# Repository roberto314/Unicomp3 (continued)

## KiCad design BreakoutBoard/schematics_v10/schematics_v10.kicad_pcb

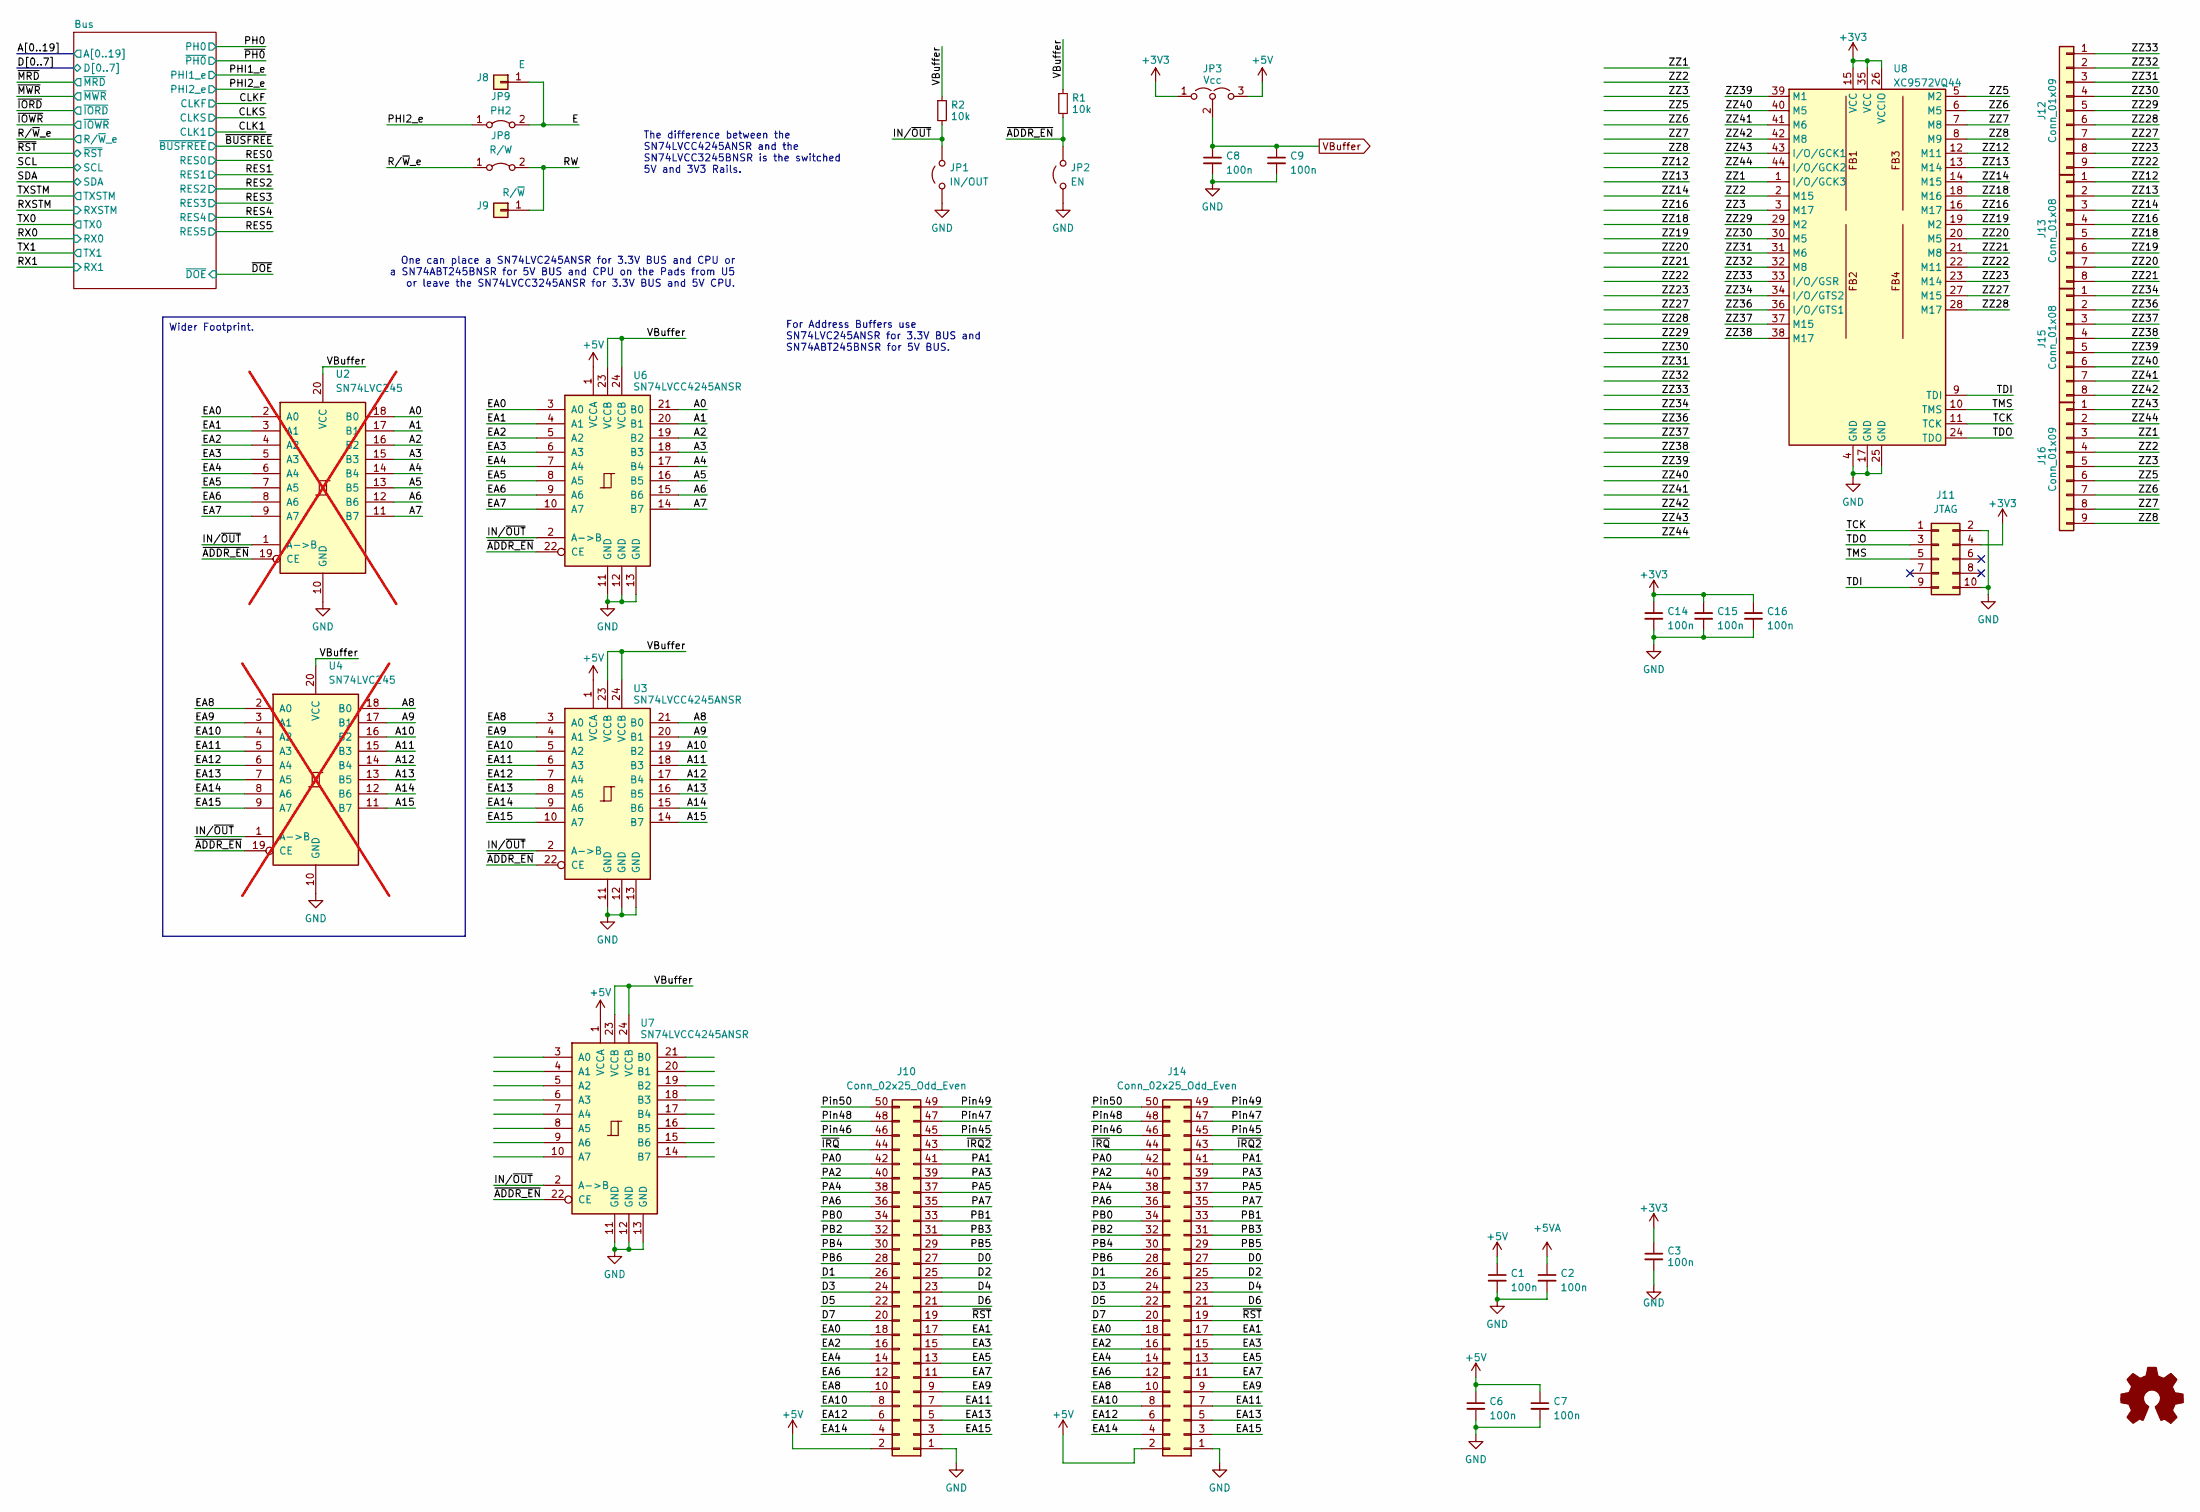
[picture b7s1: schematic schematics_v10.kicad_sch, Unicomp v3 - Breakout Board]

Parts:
C1, C2, C3, C6, C7, C8, C9, C14, C15, C16: 100n; C_1206_3216Metric
J8: E; PinHeader_1x01_P2.00mm_Vertical
J9: R/~{W}; PinHeader_1x01_P2.00mm_Vertical
J10: Conn_02x25_Odd_Even; PinHeader_2x25_P2.54mm_Vertical
J11: JTAG; PinHeader_2x05_P2.54mm_Horizontal
J12, J16: Conn_01x09; PinHeader_1x09_P2.54mm_Vertical
J13, J15: Conn_01x08; PinHeader_1x08_P2.54mm_Vertical
J14: Conn_02x25_Odd_Even; PinHeader_2x25_P2.54mm_Horizontal
JP1: IN/OUT; PinHeader_1x02_P2.54mm_Vertical
JP2: EN; PinHeader_1x02_P2.54mm_Vertical
JP3: Vcc; SolderJumper-3_P1.3mm_Open_RoundedPad1.0x1.5mm_NumberLabels
JP8: R/W; SolderJumper-2_P1.3mm_Bridged_RoundedPad1.0x1.5mm
JP9: PH2; SolderJumper-2_P1.3mm_Bridged_RoundedPad1.0x1.5mm
R1, R2: 10k; R_1206_3216Metric_Pad1.30x1.75mm_HandSolder
U2, U4: SN74LVC245; SO-20_12.8x7.5mm_P1.27mm; not fitted
U3, U6, U7: SN74LVCC4245ANSR; SO-24_5.3x15mm_P1.27mm
U8: XC9572VQ44; TQFP-44_10x10mm_P0.8mm

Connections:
+3V3: C3.1, C14.1, C15.1, C16.1, J11.4, JP3.1 (A), U8.15 (VCC), U8.26 (VCCIO), U8.35 (VCC); also elsewhere on the board
+5V: C1.1, C6.1, C7.1, J10.2, J14.2, JP3.3 (B), U3.1 (VCCA), U6.1 (VCCA), U7.1 (VCCA); also elsewhere on the board
+5VA: C2.1; also elsewhere on the board
/A0: U2.18 (B0), U6.21 (B0); also elsewhere on the board
/A1: U2.17 (B1), U6.20 (B1); also elsewhere on the board
/A2: U2.16 (B2), U6.19 (B2); also elsewhere on the board
/A3: U2.15 (B3), U6.18 (B3); also elsewhere on the board
/A4: U2.14 (B4), U6.17 (B4); also elsewhere on the board
/A5: U2.13 (B5), U6.16 (B5); also elsewhere on the board
/A6: U2.12 (B6), U6.15 (B6); also elsewhere on the board
/A7: U2.11 (B7), U6.14 (B7); also elsewhere on the board
/A8: U3.21 (B0), U4.18 (B0); also elsewhere on the board
/A9: U3.20 (B1), U4.17 (B1); also elsewhere on the board
/A10: U3.19 (B2), U4.16 (B2); also elsewhere on the board
/A11: U3.18 (B3), U4.15 (B3); also elsewhere on the board
/A12: U3.17 (B4), U4.14 (B4); also elsewhere on the board
/A13: U3.16 (B5), U4.13 (B5); also elsewhere on the board
/A14: U3.15 (B6), U4.12 (B6); also elsewhere on the board
/A15: U3.14 (B7), U4.11 (B7); also elsewhere on the board
/D0: J10.27, J14.27; also elsewhere on the board
/D1: J10.26, J14.26; also elsewhere on the board
/D2: J10.25, J14.25; also elsewhere on the board
/D3: J10.24, J14.24; also elsewhere on the board
/D4: J10.23, J14.23; also elsewhere on the board
/D5: J10.22, J14.22; also elsewhere on the board
/D6: J10.21, J14.21; also elsewhere on the board
/D7: J10.20, J14.20; also elsewhere on the board
/E: J8.1, JP9.2 (B)
/EA0: J10.18, J14.18, U2.2 (A0), U6.3 (A0)
/EA1: J10.17, J14.17, U2.3 (A1), U6.4 (A1)
/EA2: J10.16, J14.16, U2.4 (A2), U6.5 (A2)
/EA3: J10.15, J14.15, U2.5 (A3), U6.6 (A3)
/EA4: J10.14, J14.14, U2.6 (A4), U6.7 (A4)
/EA5: J10.13, J14.13, U2.7 (A5), U6.8 (A5)
/EA6: J10.12, J14.12, U2.8 (A6), U6.9 (A6)
/EA7: J10.11, J14.11, U2.9 (A7), U6.10 (A7)
/EA8: J10.10, J14.10, U3.3 (A0), U4.2 (A0)
/EA9: J10.9, J14.9, U3.4 (A1), U4.3 (A1)
/EA10: J10.8, J14.8, U3.5 (A2), U4.4 (A2)
/EA11: J10.7, J14.7, U3.6 (A3), U4.5 (A3)
/EA12: J10.6, J14.6, U3.7 (A4), U4.6 (A4)
/EA13: J10.5, J14.5, U3.8 (A5), U4.7 (A5)
/EA14: J10.4, J14.4, U3.9 (A6), U4.8 (A6)
/EA15: J10.3, J14.3, U3.10 (A7), U4.9 (A7)
/IN/~OUT: JP1.2 (B), R2.2, U2.1 (A->B), U3.2 (A->B), U4.1 (A->B), U6.2 (A->B), U7.2 (A->B)
/PA0: J10.42, J14.42
/PA1: J10.41, J14.41
/PA2: J10.40, J14.40
/PA3: J10.39, J14.39
/PA4: J10.38, J14.38
/PA5: J10.37, J14.37
/PA6: J10.36, J14.36
/PA7: J10.35, J14.35
/PB0: J10.34, J14.34
/PB1: J10.33, J14.33
/PB2: J10.32, J14.32
/PB3: J10.31, J14.31
/PB4: J10.30, J14.30
/PB5: J10.29, J14.29
/PB6: J10.28, J14.28
/PHI2_e: JP9.1 (A); also elsewhere on the board
/Pin45: J10.45, J14.45
/Pin46: J10.46, J14.46
/Pin47: J10.47, J14.47
/Pin48: J10.48, J14.48
/Pin49: J10.49, J14.49
/Pin50: J10.50, J14.50
/RW: J9.1, JP8.2 (B)
/R/~W_e: JP8.1 (A); also elsewhere on the board
/TCK: J11.1, U8.11 (TCK)
/TDI: J11.9, U8.9 (TDI)
/TDO: J11.3, U8.24 (TDO)
/TMS: J11.5, U8.10 (TMS)
/ZZ1: J16.3, U8.1 (I/O/GCK3)
/ZZ2: J16.4, U8.2 (M15)
/ZZ3: J16.5, U8.3 (M17)
/ZZ5: J16.6, U8.5 (M2)
/ZZ6: J16.7, U8.6 (M5)
/ZZ7: J16.8, U8.7 (M8)
/ZZ8: J16.9, U8.8 (M9)
/ZZ12: J13.1, U8.12 (M11)
/ZZ13: J13.2, U8.13 (M14)
/ZZ14: J13.3, U8.14 (M15)
/ZZ16: J13.4, U8.16 (M17)
/ZZ18: J13.5, U8.18 (M16)
/ZZ19: J13.6, U8.19 (M2)
/ZZ20: J13.7, U8.20 (M5)
/ZZ21: J13.8, U8.21 (M8)
/ZZ22: J12.9, U8.22 (M11)
/ZZ23: J12.8, U8.23 (M14)
/ZZ27: J12.7, U8.27 (M15)
/ZZ28: J12.6, U8.28 (M17)
/ZZ29: J12.5, U8.29 (M2)
/ZZ30: J12.4, U8.30 (M5)
/ZZ31: J12.3, U8.31 (M6)
/ZZ32: J12.2, U8.32 (M8)
/ZZ33: J12.1, U8.33 (I/O/GSR)
/ZZ34: J15.1, U8.34 (I/O/GTS2)
/ZZ36: J15.2, U8.36 (I/O/GTS1)
/ZZ37: J15.3, U8.37 (M15)
/ZZ38: J15.4, U8.38 (M17)
/ZZ39: J15.5, U8.39 (M1)
/ZZ40: J15.6, U8.40 (M5)
/ZZ41: J15.7, U8.41 (M6)
/ZZ42: J15.8, U8.42 (M8)
/ZZ43: J16.1, U8.43 (I/O/GCK1)
/ZZ44: J16.2, U8.44 (I/O/GCK2)
/~ADDR_EN: JP2.2 (B), R1.2, U2.19 (CE), U3.22 (CE), U4.19 (CE), U6.22 (CE), U7.22 (CE)
/~IRQ2: J10.43, J14.43
/~IRQ: J10.44, J14.44
/~RST: J10.19, J14.19; also elsewhere on the board
GND: C1.2, C2.2, C3.2, C6.2, C7.2, C8.2, C9.2, C14.2, C15.2, C16.2, J10.1, J11.2, J11.10, J14.1, JP1.1 (A), JP2.1 (A), U2.10 (GND), U3.11 (GND), U3.12 (GND), U3.13 (GND), U4.10 (GND), U6.11 (GND), U6.12 (GND), U6.13 (GND), U7.11 (GND), U7.12 (GND), U7.13 (GND), U8.4 (GND), U8.17 (GND), U8.25 (GND); also elsewhere on the board
VBuffer: C8.1, C9.1, JP3.2 (C), R1.1, R2.1, U2.20 (VCC), U3.23 (VCCB), U3.24 (VCCB), U4.20 (VCC), U6.23 (VCCB), U6.24 (VCCB), U7.23 (VCCB), U7.24 (VCCB); also elsewhere on the board

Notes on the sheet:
Wider Footprint.
For Address Buffers use SN74LVC245ANSR for 3.3V BUS and SN74ABT245BNSR for 5V BUS.
One can place a SN74LVC245ANSR for 3.3V BUS and CPU or a SN74ABT245BNSR for 5V BUS and CPU on the Pads from U5 or leave the SN74LVCC3245ANSR for 3.3V BUS and 5V CPU.
The difference between the SN74LVCC4245ANSR and the SN74LVCC3245BNSR is the switched 5V and 3V3 Rails.

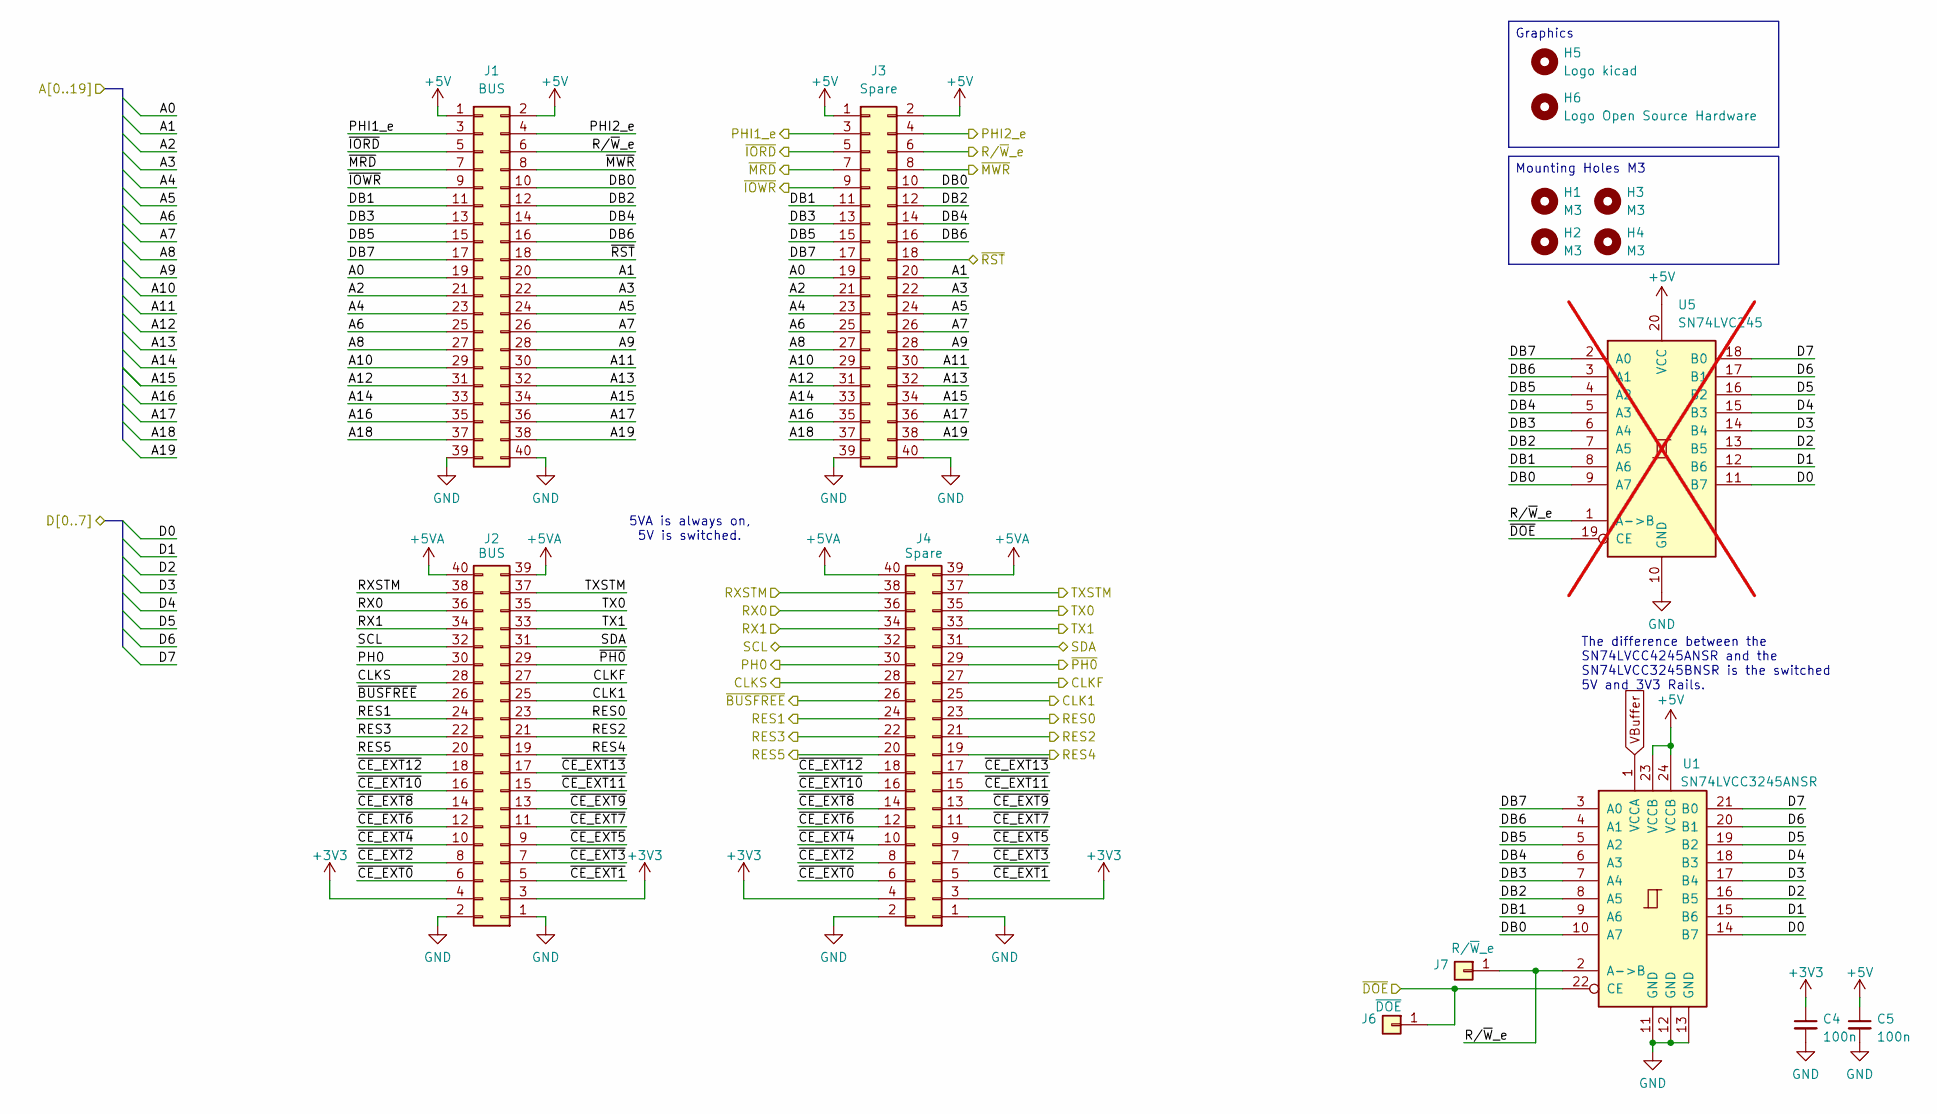
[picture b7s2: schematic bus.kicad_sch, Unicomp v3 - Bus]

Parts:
C4, C5: 100n; C_1206_3216Metric
H1, H2, H3, H4: M3; MountingHole_3.2mm_M3
H5: Logo kicad; KiCad-Logo2_6mm_SilkScreen
H6: Logo Open Source Hardware; OSHW-Logo2_7.3x6mm_SilkScreen
J1, J2: BUS; PinSocket_2x20_P2.54mm_Vertical
J3, J4: Spare; PinSocket_2x20_P2.54mm_Vertical
J6: ~{DOE}; PinHeader_1x01_P2.00mm_Vertical
J7: R/~{W}_e; PinHeader_1x01_P2.00mm_Vertical
U1: SN74LVCC3245ANSR; SO-24_5.3x15mm_P1.27mm
U5: SN74LVC245; SO-20_12.8x7.5mm_P1.27mm; not fitted

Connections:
+3V3: C4.1, J2.3, J2.4, J4.3, J4.4; also elsewhere on the board
+5V: C5.1, J1.1, J1.2, J3.1, J3.2, U1.23 (VCCB), U1.24 (VCCB), U5.20 (VCC); also elsewhere on the board
+5VA: J2.39, J2.40, J4.39, J4.40; also elsewhere on the board
/A0: J1.19, J3.19; also elsewhere on the board
/A1: J1.20, J3.20; also elsewhere on the board
/A2: J1.21, J3.21; also elsewhere on the board
/A3: J1.22, J3.22; also elsewhere on the board
/A4: J1.23, J3.23; also elsewhere on the board
/A5: J1.24, J3.24; also elsewhere on the board
/A6: J1.25, J3.25; also elsewhere on the board
/A7: J1.26, J3.26; also elsewhere on the board
/A8: J1.27, J3.27; also elsewhere on the board
/A9: J1.28, J3.28; also elsewhere on the board
/A10: J1.29, J3.29; also elsewhere on the board
/A11: J1.30, J3.30; also elsewhere on the board
/A12: J1.31, J3.31; also elsewhere on the board
/A13: J1.32, J3.32; also elsewhere on the board
/A14: J1.33, J3.33; also elsewhere on the board
/A15: J1.34, J3.34; also elsewhere on the board
/A16: J1.35, J3.35
/A17: J1.36, J3.36
/A18: J1.37, J3.37
/A19: J1.38, J3.38
/Bus/DB0: J1.10, J3.10, U1.10 (A7), U5.9 (A7)
/Bus/DB1: J1.11, J3.11, U1.9 (A6), U5.8 (A6)
/Bus/DB2: J1.12, J3.12, U1.8 (A5), U5.7 (A5)
/Bus/DB3: J1.13, J3.13, U1.7 (A4), U5.6 (A4)
/Bus/DB4: J1.14, J3.14, U1.6 (A3), U5.5 (A3)
/Bus/DB5: J1.15, J3.15, U1.5 (A2), U5.4 (A2)
/Bus/DB6: J1.16, J3.16, U1.4 (A1), U5.3 (A1)
/Bus/DB7: J1.17, J3.17, U1.3 (A0), U5.2 (A0)
/Bus/~CE_EXT0: J2.6, J4.6
/Bus/~CE_EXT1: J2.5, J4.5
/Bus/~CE_EXT2: J2.8, J4.8
/Bus/~CE_EXT3: J2.7, J4.7
/Bus/~CE_EXT4: J2.10, J4.10
/Bus/~CE_EXT5: J2.9, J4.9
/Bus/~CE_EXT6: J2.12, J4.12
/Bus/~CE_EXT7: J2.11, J4.11
/Bus/~CE_EXT8: J2.14, J4.14
/Bus/~CE_EXT9: J2.13, J4.13
/Bus/~CE_EXT10: J2.16, J4.16
/Bus/~CE_EXT11: J2.15, J4.15
/Bus/~CE_EXT12: J2.18, J4.18
/Bus/~CE_EXT13: J2.17, J4.17
/CLK1: J2.25, J4.25
/CLKF: J2.27, J4.27
/CLKS: J2.28, J4.28
/D0: U1.14 (B7), U5.11 (B7); also elsewhere on the board
/D1: U1.15 (B6), U5.12 (B6); also elsewhere on the board
/D2: U1.16 (B5), U5.13 (B5); also elsewhere on the board
/D3: U1.17 (B4), U5.14 (B4); also elsewhere on the board
/D4: U1.18 (B3), U5.15 (B3); also elsewhere on the board
/D5: U1.19 (B2), U5.16 (B2); also elsewhere on the board
/D6: U1.20 (B1), U5.17 (B1); also elsewhere on the board
/D7: U1.21 (B0), U5.18 (B0); also elsewhere on the board
/PH0: J2.30, J4.30
/PHI1_e: J1.3, J3.3
/PHI2_e: J1.4, J3.4; also elsewhere on the board
/RES0: J2.23, J4.23
/RES1: J2.24, J4.24
/RES2: J2.21, J4.21
/RES3: J2.22, J4.22
/RES4: J2.19, J4.19
/RES5: J2.20, J4.20
/RX0: J2.36, J4.36
/RX1: J2.34, J4.34
/RXSTM: J2.38, J4.38
/R/~W_e: J1.6, J3.6, J7.1, U1.2 (A->B), U5.1 (A->B); also elsewhere on the board
/SCL: J2.32, J4.32
/SDA: J2.31, J4.31
/TX0: J2.35, J4.35
/TX1: J2.33, J4.33
/TXSTM: J2.37, J4.37
/~BUSFREE: J2.26, J4.26
/~DOE: J6.1, U1.22 (CE), U5.19 (CE)
/~IORD: J1.5, J3.5
/~IOWR: J1.9, J3.9
/~MRD: J1.7, J3.7
/~MWR: J1.8, J3.8
/~PH0: J2.29, J4.29
/~RST: J1.18, J3.18; also elsewhere on the board
GND: C4.2, C5.2, J1.39, J1.40, J2.1, J2.2, J3.39, J3.40, J4.1, J4.2, U1.11 (GND), U1.12 (GND), U1.13 (GND), U5.10 (GND); also elsewhere on the board
VBuffer: U1.1 (VCCA); also elsewhere on the board

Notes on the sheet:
Graphics
5VA is always on, 5V is switched.
Mounting Holes M3
The difference between the SN74LVCC4245ANSR and the SN74LVCC3245BNSR is the switched 5V and 3V3 Rails.

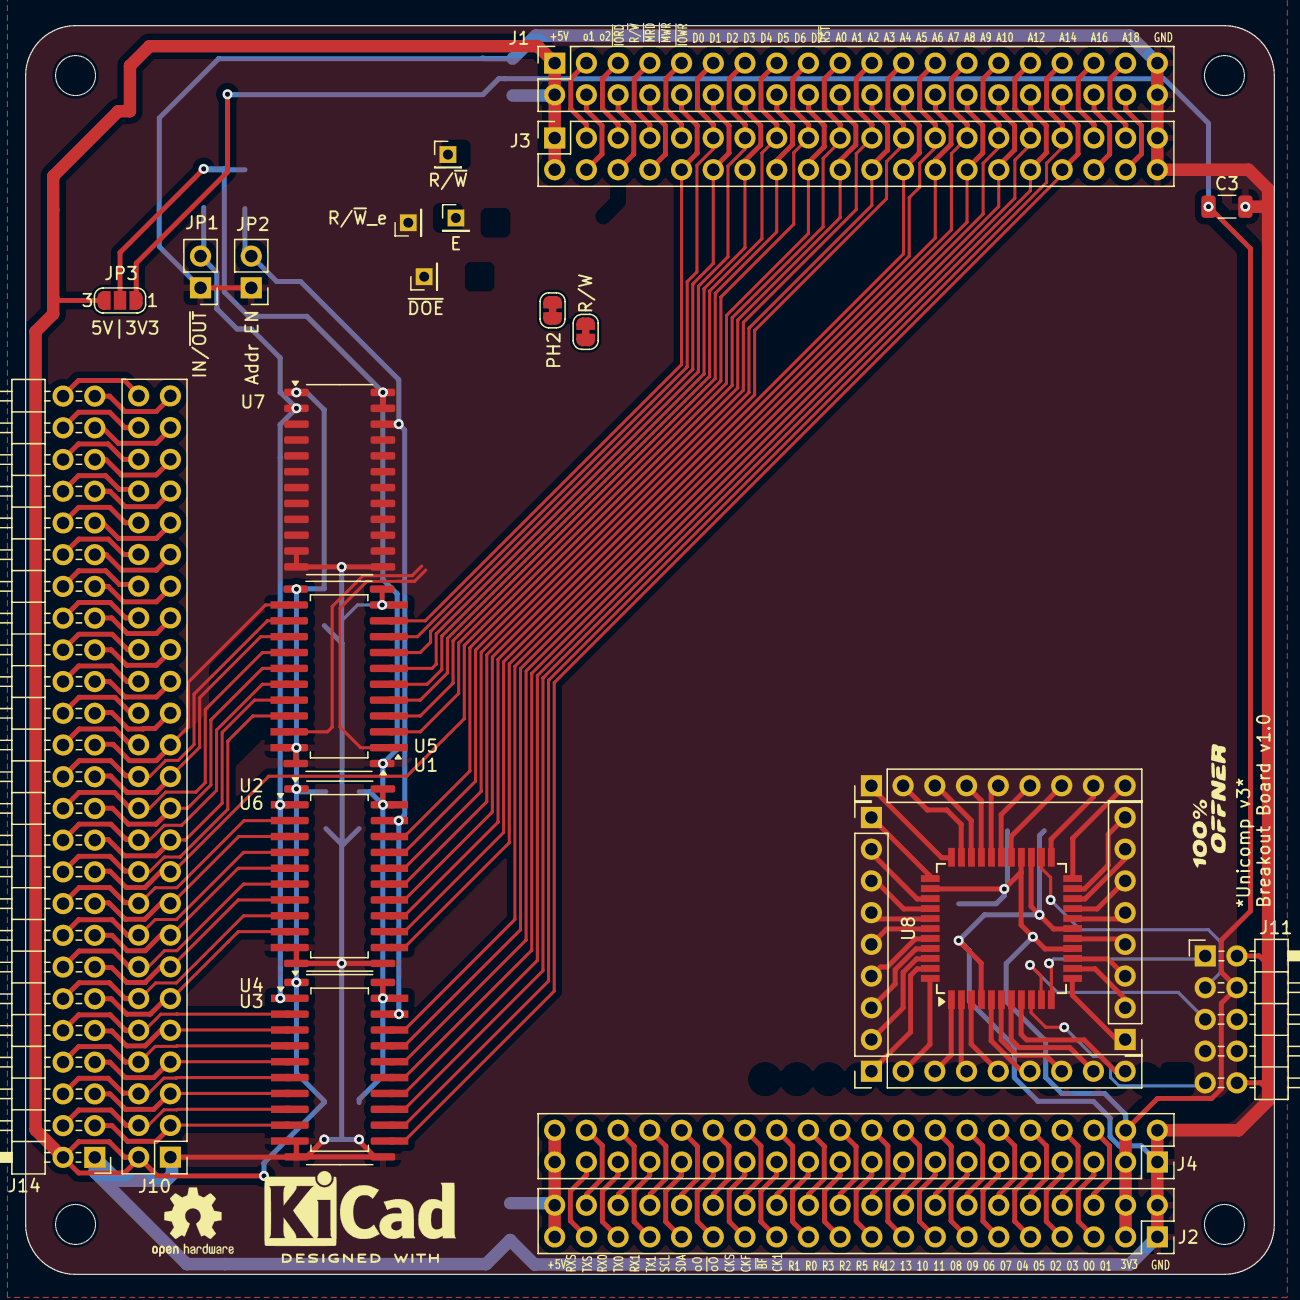
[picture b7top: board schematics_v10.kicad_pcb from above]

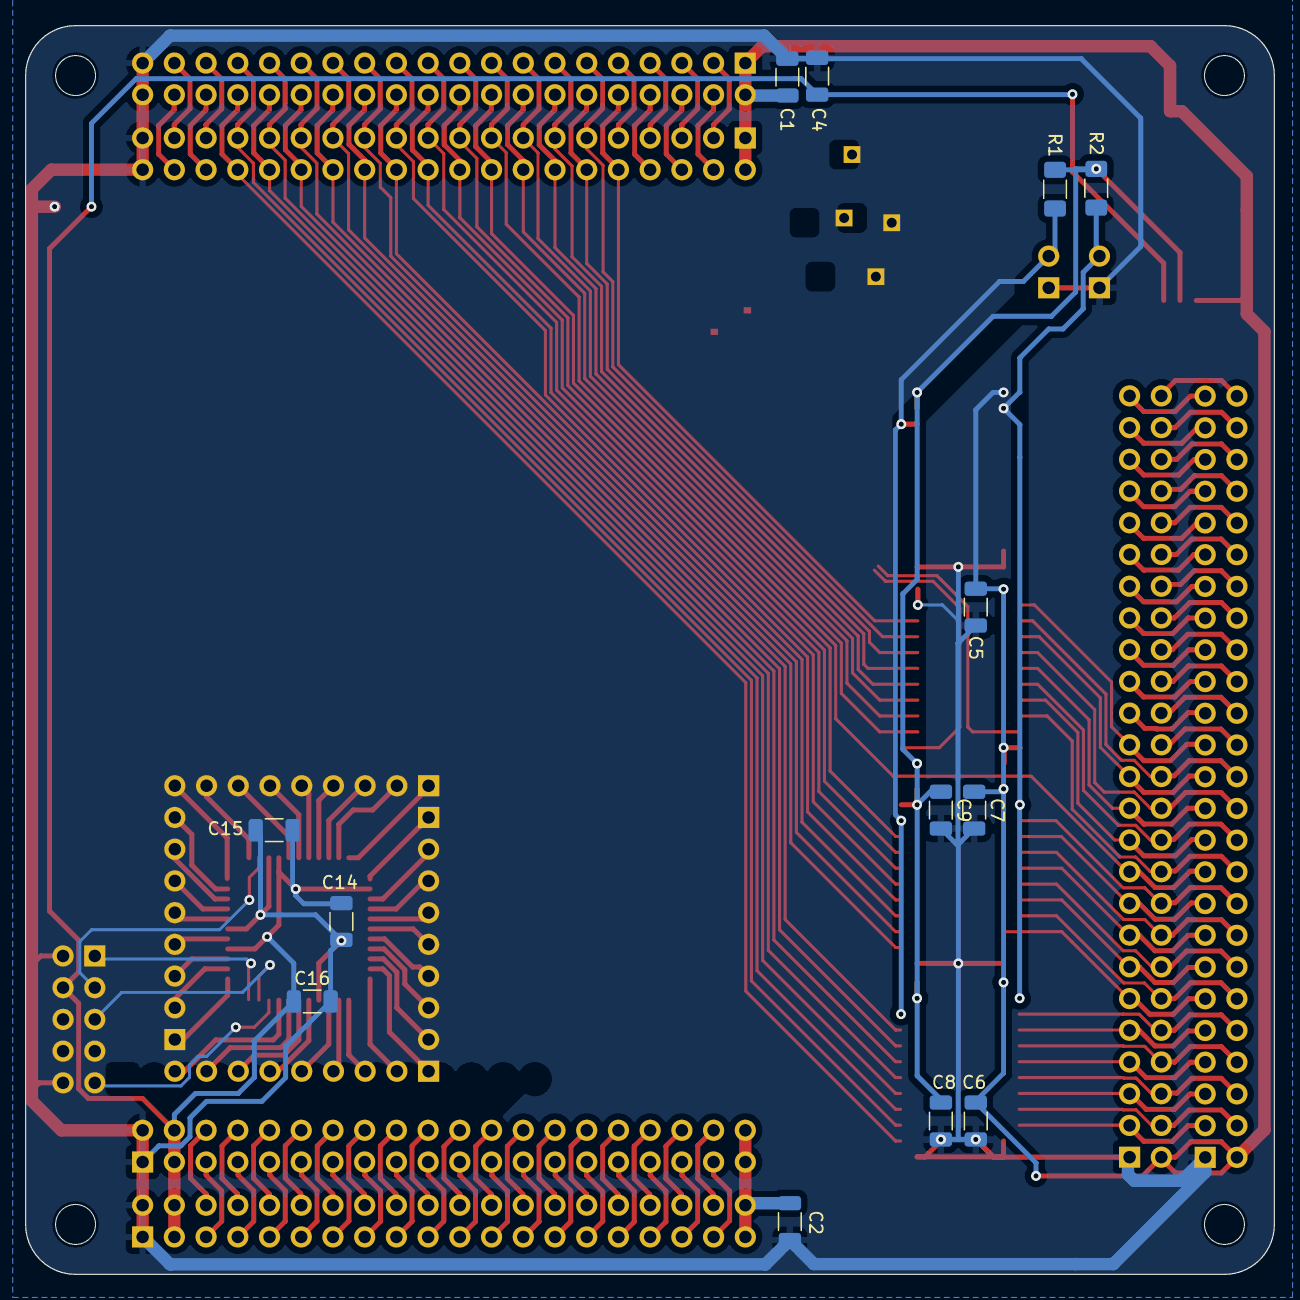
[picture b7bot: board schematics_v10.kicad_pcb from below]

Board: 2 copper layers, 100.0 x 100.0 mm, 48 parts (13 on the bottom side), 165 nets.
